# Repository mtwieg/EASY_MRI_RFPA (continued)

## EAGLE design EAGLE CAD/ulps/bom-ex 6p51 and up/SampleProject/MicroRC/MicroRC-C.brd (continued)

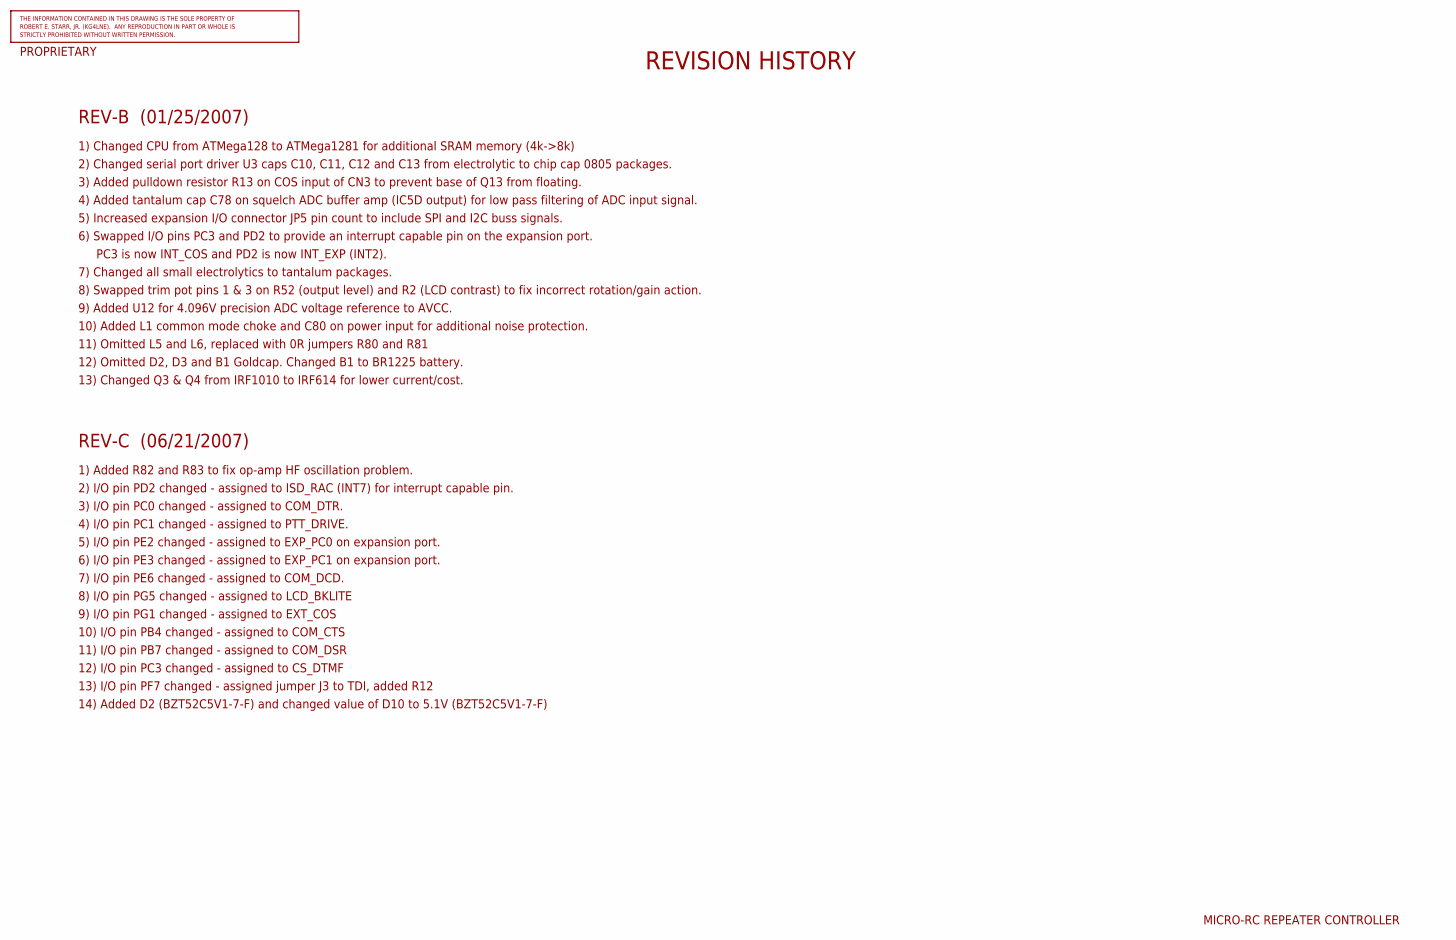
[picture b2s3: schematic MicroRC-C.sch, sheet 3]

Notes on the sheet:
MICRO-RC REPEATER CONTROLLER
REVISION HISTORY
REV-B (01/25/2007)
2) Changed serial port driver U3 caps C10, C11, C12 and C13 from electrolytic to chip cap 0805 packages.
4) Added tantalum cap C78 on squelch ADC buffer amp (IC5D output) for low pass filtering of ADC input signal.
5) Increased expansion I/O connector JP5 pin count to include SPI and I2C buss signals.
3) Added pulldown resistor R13 on COS input of CN3 to prevent base of Q13 from floating.
6) Swapped I/O pins PC3 and PD2 to provide an interrupt capable pin on the expansion port.
PC3 is now INT_COS and PD2 is now INT_EXP (INT2).
7) Changed all small electrolytics to tantalum packages.
8) Swapped trim pot pins 1 & 3 on R52 (output level) and R2 (LCD contrast) to fix incorrect rotation/gain action.
9) Added U12 for 4.096V precision ADC voltage reference to AVCC.
1) Changed CPU from ATMega128 to ATMega1281 for additional SRAM memory (4k->8k)
10) Added L1 common mode choke and C80 on power input for additional noise protection.
11) Omitted L5 and L6, replaced with 0R jumpers R80 and R81
12) Omitted D2, D3 and B1 Goldcap. Changed B1 to BR1225 battery.
13) Changed Q3 & Q4 from IRF1010 to IRF614 for lower current/cost.
REV-C (06/21/2007)
1) Added R82 and R83 to fix op-amp HF oscillation problem.
2) I/O pin PD2 changed - assigned to ISD_RAC (INT7) for interrupt capable pin.
5) I/O pin PE2 changed - assigned to EXP_PC0 on expansion port.
14) Added D2 (BZT52C5V1-7-F) and changed value of D10 to 5.1V (BZT52C5V1-7-F)
4) I/O pin PC1 changed - assigned to PTT_DRIVE.
6) I/O pin PE3 changed - assigned to EXP_PC1 on expansion port.
7) I/O pin PE6 changed - assigned to COM_DCD.
3) I/O pin PC0 changed - assigned to COM_DTR.
8) I/O pin PG5 changed - assigned to LCD_BKLITE
9) I/O pin PG1 changed - assigned to EXT_COS
10) I/O pin PB4 changed - assigned to COM_CTS
11) I/O pin PB7 changed - assigned to COM_DSR
13) I/O pin PF7 changed - assigned jumper J3 to TDI, added R12
12) I/O pin PC3 changed - assigned to CS_DTMF

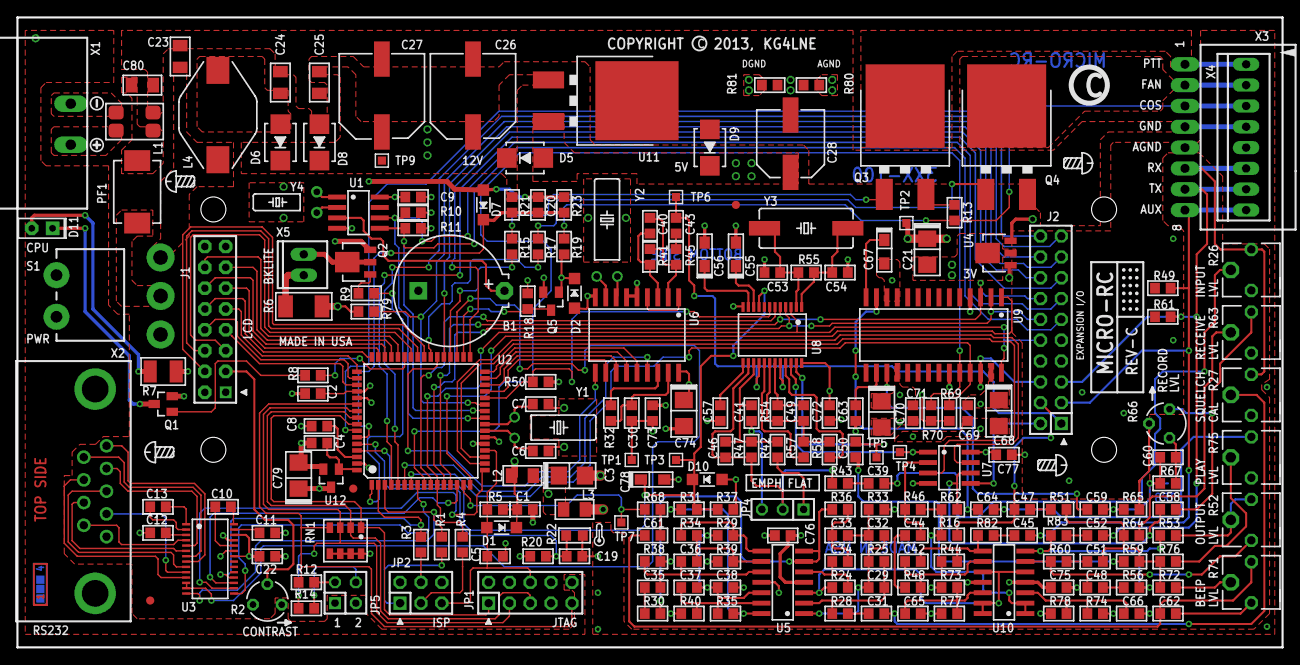
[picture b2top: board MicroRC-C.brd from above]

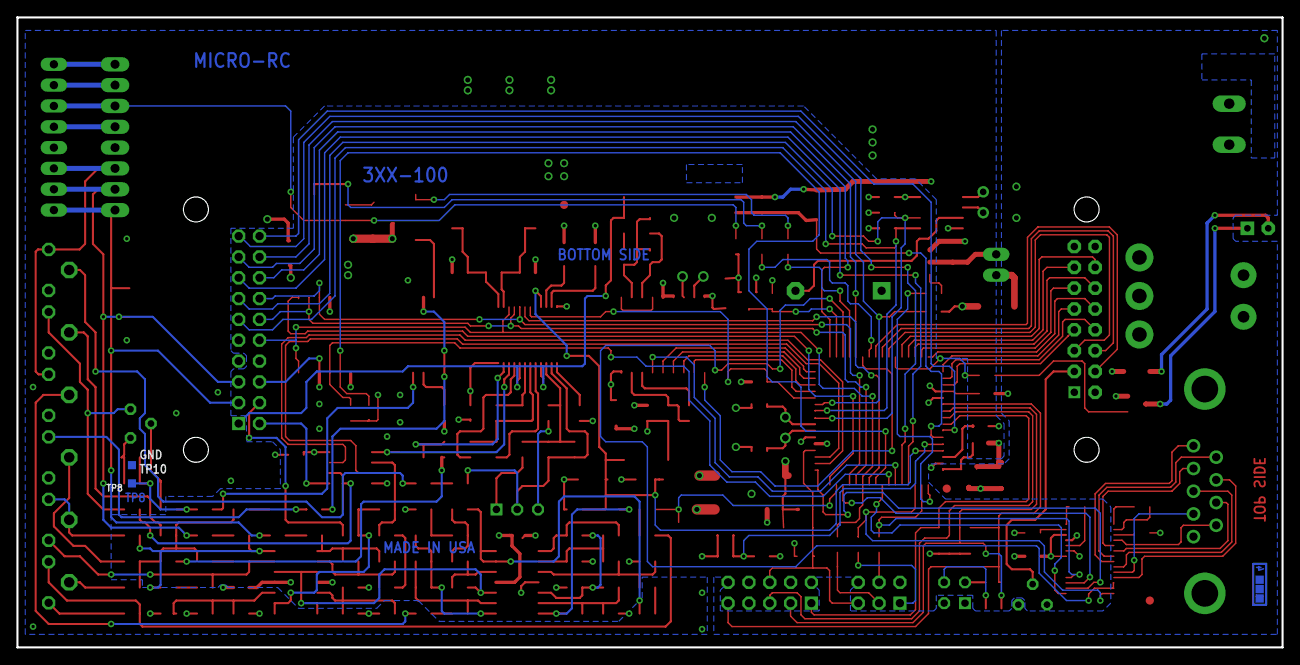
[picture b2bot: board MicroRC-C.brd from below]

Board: 4 copper layers, 154.3 x 76.8 mm, 254 parts (3 on the bottom side), 186 nets.

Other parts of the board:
U$6: ICON_ATTR_COPYRIGHT
U$7: LAYER_CHECK-4
U$60: FIELD_ATTR_DATECODE5_RESTRICT
U$74: ICON_SIDE_BOTTOM
U$75: ICON_SIDE_TOP
U$100: ICON_ATTR_REV-M
U$102: FAB_8X14
U$105: FAB_DOCFIELD
U$112: ICON_TEMP
U$123: ICON_MINUS
U$124: 3.0250; FAB_ARROW_LINE025
U$125: ICON_PLUS
U$128, U$136: 0,0; FAB_ARROW_LINE025
U$132: 2.7125; FAB_CONST_LINE050
U$133, U$239, U$282, U$283: ICON_MSCREW-S
U$138: 6.0750; FAB_ARROW_LINE025
U$139: 0.5750; FAB_CONST_LINE050
U$140: 1.2125; FAB_CONST_LINE050
U$141: 1.5125; FAB_CONST_LINE050
U$142: 1.8125; FAB_CONST_LINE050
U$143: 2.1125; FAB_CONST_LINE050
U$144: 2.4125; FAB_CONST_LINE050
U$145: 1.3375; FAB_CONST_LINE050
U$146: 2.2750; FAB_CONST_LINE050
U$230, U$235, U$280, U$281: ICON_PIN1_B
U$240, U$241: ICON_ARROW-T

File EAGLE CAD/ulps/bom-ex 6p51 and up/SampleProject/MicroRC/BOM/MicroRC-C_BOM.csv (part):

Qty-1,Part References,Value,Package,Mfg Part Num,Mfg Name,VID,Vendor Part Num,Description,Pkg Code,XREF
18,"C2, C8, C9, C10, C19, C20, C30, C31, C43, C57, C63, C69, C71, C72, C73, C75, C76, C77",0.1uF,C0805,C0805F104K5RACTU,Kemet,DK,399-5110-1-ND,CAP CER .1UF 50V X7R 0805 FO,0805,REF69
3,"C23, C24, C25",0.1uF,C1206,C1206C104K5RACTU,Kemet,DK,399-1249-1-ND,CAP .10UF 50V CERAMIC X7R 1206,1206,REF67
0,"C78(DNP)",0.1uF,C3216/T,DNP,DO NOT PLACE,(N/A),DO NOT PLACE,DO NOT PLACE,*,REF14
1,"C55",0.1uF,C3216/T,T491A104K035AT,Kemet,DK,399-3676-1-ND,CAPACITOR TANT .10UF 35V 10% SMD,*,REF22
1,"L2",0.1uH,L1206,PM1210-R10J,JW Miller A Bourns Company,DK,M6093CT-ND,INDUCTOR .10UH 5% 1210 SMD,*,REF20
1,"C80",0.01uF,C1206,12065C103KAT2A,AVX Corporation,DK,478-1542-1-ND,CAP CERM .01UF 10% 50V X7R 1206,*,REF3
1,"C5",0.01uF,C0805,C0805C103K5RACTU,Kemet,DK,399-1158-1-ND,CAP 10000PF 50V CERAMIC X7R 0805,0805,REF66
3,"C11, C12, C13",0.47uF,C0805,C0805F474K3RACTU,Kemet,DK,399-5112-1-ND,CAP CER .47UF 25V X7R 0805 FO,0805,REF74
2,"C40, C62",0.001uF,C0805,C0805C102K5RACTU,Kemet,DK,399-1147-1-ND,CAP 1000PF 50V CERAMIC X7R 0805,0805,REF65
2,"C35, C38",0.047uF,C0805,C0805C473K5RACTU,Kemet,DK,399-1166-1-ND,CAP 47000PF 50V CERAMIC X7R 0805,0805,REF68
1,"C41",0.0068uF,C0805,C0805C682K5RACTU,Kemet,DK,399-1157-1-ND,CAP 6800PF 50V CERAMIC X7R 0805,0805,REF79
2,"R80, R81",0R,R0805,RC0805JR-070RL,Yageo,DK,311-0.0ARCT-ND,RES 0.0 OHM 1/8W 5% 0805 SMD,0805,REF92
2,"R82, R83",1.00K,R0805,ERJ-6ENF1001V,Panasonic - ECG,DK,P1.00KCCT-ND,RES 1.00K OHM 1/8W 1% 0805 SMD,0805,REF45
4,"R16, R46, R55, R62",1M,R0805,ERJ-6ENF1004V,Panasonic - ECG,DK,P1.00MCCT-ND,RES 1.00M OHM 1/8W 1% 0805 SMD,0805,REF46
14,"C1, C22, C39, C44, C45, C47, C50, C52, C58, C59, C61, C64, C65, C66",1uF,C0805,C0805C105Z3VACTU,Kemet,DK,399-1293-1-ND,CAP 1.0UF 25V CERAMIC Y5V 0805,0805,REF73
1,"C67",1uF,C3216/T,T491A105K016AT,Kemet,DK,399-3678-1-ND,CAPACITOR TANT 1.0UF 16V 10% SMD,*,REF23
1,"C56",2.2uF,C3216/T,T491A225K010AT,Kemet,DK,399-3690-1-ND,CAPACITOR TANT 2.2UF 10V 10% SMD,*,REF24
1,"Y2",3.579 MHZ,TC310H,ECS-35-18-10X,ECS Inc,DK,XC1371-ND,CRYSTAL 3.579545 MHZ 18PF CYL,*,REF17
7,"R8, R9, R15, R17, R19, R30, R33",4.75K,R0805,ERJ-6ENF4751V,Panasonic - ECG,DK,P4.75KCCT-ND,RES 4.75K OHM 1/8W 1% 0805 SMD,0805,REF55
1,"Y3",4.032MHZ,SM49,ECS-40.3-20-5PX-TR,ECS Inc,DK,XC1258CT-ND,CRYSTAL 4.032MHZ 20PF SMD,*,REF16
1,"D2",5.1V,SOD123,BZT52C5V1-7-F,Diodes Inc,DK,BZT52C5V1-FDITR-ND,DIODE ZENER 5.1V 500MW SOD-123,SOD123,REF10
1,"R36",5.62K,R0805,ERJ-6ENF5621V,Panasonic - ECG,DK,P5.62KCCT-ND,RES 5.62K OHM 1/8W 1% 0805 SMD,0805,REF59
1,"R38",8.25K,R0805,ERJ-6ENF8251V,Panasonic - ECG,DK,P8.25KCCT-ND,RES 8.25K OHM 1/8W 1% 0805 SMD,0805,REF61
1,"RN1",10K,744-8,744C083103JPTR,CTS Resistor Products,DK,744C083103JPCT-ND,RES ARRAY 10K OHM 8TERM 4RES SMD,*,REF8
19,"R5, R10, R11, R18, R25, R28, R39, R40, R43, R50, R54, R56, R57, R58, R65, R67, R69, R70, R79",10K,R0805,ERJ-6ENF1002V,Panasonic - ECG,DK,P10.0KCCT-ND,RES 10.0K OHM 1/8W 1% 0805 SMD,0805,REF47
5,"R26, R27, R63, R71, R75",10K,EVME-SIDE,EVM-EGGA00B14,Panasonic - ECG,DK,EGG14BK-ND,POT 10K OHM 6MM CERAMIC SIDE ADJ,*,REF42
2,"R2, R66",10K,EVM-L4G,EVM-L4GA00B14,Panasonic - ECG,DK,L4G14BK-ND,POT 10K OHM 4MM CERAMIC TOP ADJ,*,REF44
2,"C4, C51",10uF,C0805,C0805C106K9PACTU,Kemet,DK,399-3138-1-ND,CAP CERAMIC 10UF 6.3V X5R 0805,0805,REF72
3,"C3, C21, C79",10uF,C3528/T,T491B106M016AT,Kemet,DK,399-3708-1-ND,CAPACITOR TANT 10UF 16V 20% SMD,*,REF25
1,"L4",10uH,PM-13,PM3308-100M,JW Miller A Bourns Company,DK,M9719CT-ND,INDUCTOR POWER 10UH SMD,*,REF21
1,"R42",11.3K,R0805,ERJ-6ENF1132V,Panasonic - ECG,DK,P11.3KCCT-ND,RES 11.3K OHM 1/8W 1% 0805 SMD,0805,REF49
1,"Y1",16.000 MHz,TC38H,ECS-160-18-9X,ECS Inc,DK,XC1383-ND,CRYSTAL 16.000 MHZ 18PF CYL,*,REF18
1,"D8",18V,SMB,1SMB5931BT3G,ON Semiconductor,DK,1SMB5931BT3GOSTR-ND,DIODE ZENER 18V 3W SMB,*,REF36
9,"R23, R31, R44, R48, R51, R59, R64, R72, R76",22K,R0805,ERJ-6ENF2212V,Panasonic - ECG,DK,P22.1KCCT-ND,RES 22.1K OHM 1/8W 1% 0805 SMD,0805,REF51
2,"C6, C7",22pF,C0805,C0805C220J5GACTU,Kemet,DK,399-1113-1-ND,CAP CERAMIC 22PF 50V NP0 0805,0805,REF71
3,"C68, C70, C74",22uF,C3528/T,T491B226M016AT,Kemet,DK,399-3717-1-ND,CAPACITOR TANT 22UF 16V 20% SMD,*,REF26
1,"Y4",32.678 kHz,TC26H,ECS-.327-12.5-13X,ECS Inc,DK,X1124-ND,CRYSTAL 32.768 KHZ 12.5PF CYL,*,REF15
2,"R53, R60",33.2K,R0805,ERJ-6ENF3322V,Panasonic - ECG,DK,P33.2KCCT-ND,RES 33.2K OHM 1/8W 1% 0805 SMD,0805,REF53
2,"C53, C54",33pF,C0805,C0805C330J5GACTU,Kemet,DK,399-1115-1-ND,CAP CERAMIC 33PF 50V NP0 0805,0805,REF75
5,"R1, R3, R4, R12, R14",47.5R,R0805,ERJ-6ENF47R5V,Panasonic - ECG,DK,P47.5CCT-ND ,RES 47.5 OHM 1/8W 1% 0805 SMD,0805,REF57
1,"R6",48.7R,R2010,ERJ-12SF48R7U,Panasonic - ECG,DK,P48.7ACCT-ND,RES 48.7 OHM 3/4W 1% 2010 SMD,1210,REF58
1,"R21",62K,R0805,ERJ-6ENF6192V,Panasonic - ECG,DK,P61.9KCCT-ND,RES 61.9K OHM 1/8W 1% 0805 SMD,0805,REF60
1,"R24",91.0K,R0805,ERJ-6ENF9092V,Panasonic - ECG,DK,P90.9KCCT-ND,RES 90.9K OHM 1/8W 1% 0805 SMD,0805,REF62
1,"R47",93.1K,R0805,ERJ-6ENF9312V,Panasonic - ECG,DK,P93.1KCCT-ND,RES 93.1K OHM 1/8W 1% 0805 SMD,0805,REF63
13,"R13, R20, R34, R37, R41, R45, R49, R61, R68, R73, R74, R77, R78",100K,R0805,ERJ-6ENF1003V,Panasonic - ECG,DK,P100KCCT-ND,RES 100K OHM 1/8W 1% 0805 SMD,0805,REF48
3,"C29, C46, C49",100pF,C0805,C0805C101J5GACTU,Kemet,DK,399-1122-1-ND,CAP CERAMIC 100PF 50V NP0 0805,0805,REF64
1,"C28",100uF,CSV-E/F,EEE-1CA101P,Panasonic - ECG,DK,PCE3879CT-ND,CAP ELECT 100UF 16V VS SMD,*,REF80
1,"R35",150K,R0805,ERJ-6ENF1503V,Panasonic - ECG,DK,P150KCCT-ND,RES 150K OHM 1/8W 1% 0805 SMD,0805,REF50
1,"X2",182-009-112-531,NC182M9,182-009-113R531,Norcomp Inc.,DK,182-09ME-ND,CONN DB9 MALE .318"" R/A NICKEL,*,REF34
1,"R52",200K,EVME-SIDE,EVM-EGGA00B25,Panasonic - ECG,DK,EGG25BK-ND,POT 200K OHM 6MM CERAM SIDE ADJ,*,REF43
1,"R32",301K,R0805,ERJ-6ENF3013V,Panasonic - ECG,DK,P301KCCT-ND,RES 301K OHM 1/8W 1% 0805 SMD,0805,REF52
1,"R29",332K,R0805,ERJ-6ENF3323V,Panasonic - ECG,DK,P332KCCT-ND,RES 332K OHM 1/8W 1% 0805 SMD,0805,REF54
1,"R7",464R,R1210,ERJ-14NF4640U,Panasonic - ECG,DK,P464AACT-ND,RES 464 OHM 1/2W 1% 1210 SMD,1210,REF56
2,"C36, C37",470pF,C0805,C0805C471J5GACTU,Kemet,DK,399-1133-1-ND,CAP CERAMIC 470PF 50V NP0 0805,0805,REF76
2,"C26, C27",470uF,CSV-G,EEE-1EA471P,Panasonic - ECG,DK,PCE3909CT-ND,CAP ELECT 470UF 25V VS SMD,*,REF81
1,"C48",560pF,C0805,C0805C561J5GACTU,Kemet,DK,399-1134-1-ND,CAP CERAMIC 560PF 50V NP0 0805,0805,REF78
4,"C32, C33, C34, C42",1500pF,C0805,C0805C152K5RACTU,Kemet,DK,399-1150-1-ND,CAP 1500PF 50V CERAMIC X7R 0805,0805,REF70
1,"C60",4700pF,C0805,C0805C472K5RACTU,Kemet,DK,399-1155-1-ND,CAP 4700PF 50V CERAMIC X7R 0805,0805,REF77
1,"X3",70553-0007,70553-08,70553-0007,Molex Connector Corporation,DK,WM4906-ND,CONN HEADER 8POS .100 R/A GOLD,*,REF30
1,"X5",640454-2,MTA-100-2V,640454-2,Tyco Electronics ,DK,A19423-ND,CONN HEADER VERT 2POS .100 TIN,*,REF87
1,"X4",640454-8,MTA08-100,640454-8,Tyco Electronics ,DK,A19435-ND,CONN HEADER VERT 8POS .100 TIN,*,REF88
1,"U12",AD158X,SOT23,AD1584BRTZ-REEL7,Analog Devices Inc,DK,AD1584BRTZ-REEL7CT-ND,IC V-REF 4.096V SOT-23,SOT23,REF1
1,"D1",BAV16W-7-F,SOD123,BAV16W-7-F,Diodes Inc,DK,BAV16W-FDICT-ND,DIODE SWITCH 75V 400MW SOD123,SOD123,REF9
0,"B1(DNP)",BR1225A/HB,BR1225,BR1225A/HB,Panasonic - BCG,DK,P061-ND,BATTERY LITH COIN HITEMP W/LEGS,*,REF41
2,"D7, D10",BZT52C5V1-7-F,SOD123,BZT52C5V6-7-F,Diodes Inc,DK,BZT52C5V6-FDICT-ND,DIODE ZENER 5.6V 500MW SOD-123,SOD123,REF11
1,"S1",CK-A,CK-A,2M1-SP1-T2-B4-M6RE,Carling Technologies,DK,432-1164-ND,SW TOGGLE SPDT .4VA RT ANG PCB,*,REF5
1,"L1",CM1812,CM1812,CM1812R600R-10,Laird-Signal Integrity Products,DK,240-2454-1-ND,CHOKE COMMON MODE 60 OHMS SMD,*,REF27
1,"U6",CM8870CS,SO18W,MT8870DS,Zarlink,FE,MT8870DS,DTMF Decoder IC,*,REF93
1,"U1",DS1307Z,SO08,DS1307Z+,Maxim Integrated Products,DK,DS1307Z+-ND,IC RTC SERIAL 512K 8-SOIC,SO08,REF28
1,"X1",EDSTLZ951/2,951-2,EDSTLZ951/2,On Shore Technology Inc,DK,ED2427-ND,TERM BLOCK HDR 5.08MM 2POS PCB,*,REF39
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
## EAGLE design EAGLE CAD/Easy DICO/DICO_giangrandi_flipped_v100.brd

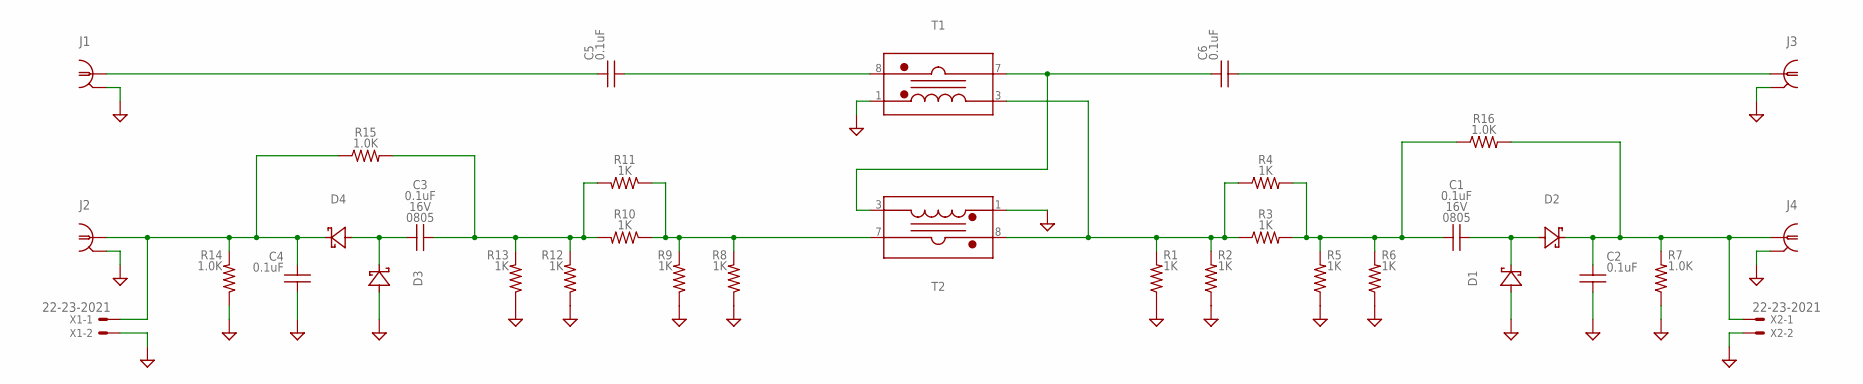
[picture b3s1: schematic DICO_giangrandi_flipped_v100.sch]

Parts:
C1, C2, C3, C4: 0.1uF; 0805_IPC-7351B
C5, C6: 0.1uF; C1812
D1, D2, D3, D4: D-SCHOTTKY1N5711W-7-FSOD123; SOD123
J1, J2, J3, J4: COAXSMA_0.375WIDE; SMA_EDGE_0.375WIDE
R1, R2, R3, R4, R5, R6, R8, R9, R10, R11, R12, R13: 1K; 1206_IPC-7351B
R7, R14, R15, R16: 1.0K; 0805_IPC-7351B
T1, T2: TRAFO_CURRENTSENSEPA1005_NOCENTERPADS; PA1005_NOCENTERPADS
X1, X2: 22-23-2021

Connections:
GND: C2.2, C4.2, D1.A (A1), D3.A (A1), J1.S1 (GND1), J1.S2 (GND1), J1.S3 (GND1), J1.S4 (GND1), J2.S1 (GND1), J2.S2 (GND1), J2.S3 (GND1), J2.S4 (GND1), J3.S1 (GND1), J3.S2 (GND1), J3.S3 (GND1), J3.S4 (GND1), J4.S1 (GND1), J4.S2 (GND1), J4.S3 (GND1), J4.S4 (GND1), R1.2, R2.2, R5.2, R6.2, R7.2, R8.2, R9.2, R12.2, R13.2, R14.2, T1.1 (SS), T2.1 (SS), X1.2, X2.2
unnamed: R8.1, R9.1, R10.1, R11.1, T2.7 (PF)
unnamed: C5.2, T1.8 (PS)
unnamed: C5.1, J1.C (1)
unnamed: C1.1, R3.2, R4.2, R5.1, R6.1, R16.1
unnamed: C1.2, D1.K (C1), D2.A (A1)
unnamed: C2.1, D2.K (C1), J4.C (1), R7.1, R16.2, X2.1
unnamed: C3.1, R10.2, R11.2, R12.1, R13.1, R15.2
unnamed: C3.2, D3.K (C1), D4.A (A1)
unnamed: C4.1, D4.K (C1), J2.C (1), R14.1, R15.1, X1.1
unnamed: C6.2, J3.C (1)
unnamed: R1.1, R2.1, R3.1, R4.1, T1.3 (SF), T2.8 (PS)
unnamed: C6.1, T1.7 (PF), T2.3 (SF)

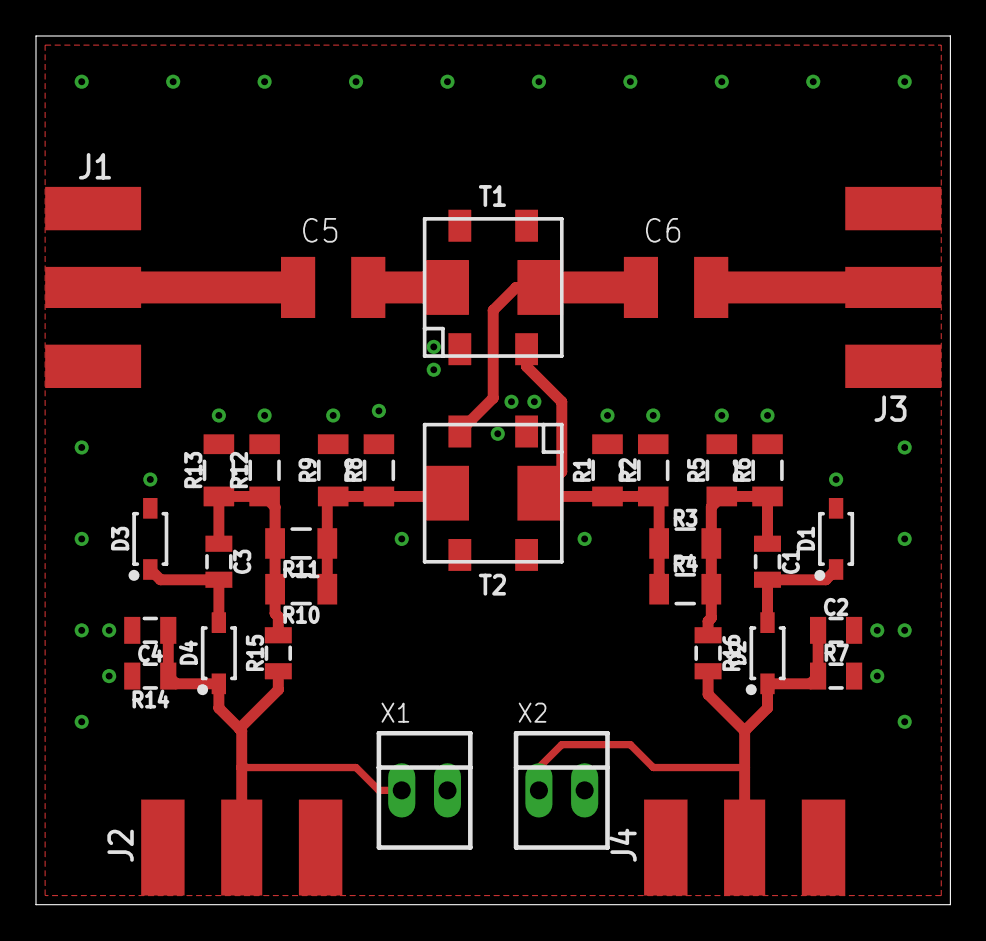
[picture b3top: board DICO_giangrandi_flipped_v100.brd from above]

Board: 2 copper layers, 50.8 x 48.3 mm, 34 parts (0 on the bottom side), 13 nets.

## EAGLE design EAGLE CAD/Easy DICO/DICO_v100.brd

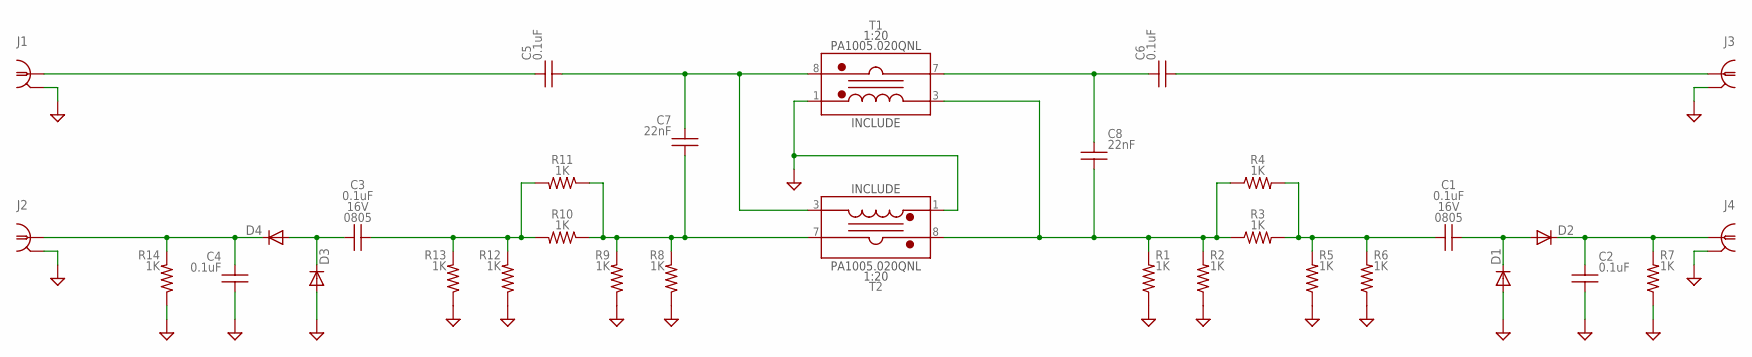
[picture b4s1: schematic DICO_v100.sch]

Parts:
C1, C2, C3, C4: 0.1uF; 0805_IPC-7351B
C5, C6: 0.1uF; C1812
C7, C8: 22nF; C1206
D1, D2, D3, D4: DIODE-SOD123; SOD123
J1, J2, J3, J4: COAXBNC_EDGE; BNC_EDGE
R1, R2, R3, R4, R5, R6, R7, R8, R9, R10, R11, R12, R13, R14: 1K; R1206
T1, T2: TRAFO_CURRENTSENSEPA1005.020QNLPA1005; PA1005

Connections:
GND: C2.2, C4.2, D1.A, D3.A, J1.G1 (GND1), J1.G2 (GND1), J1.G3 (GND1), J1.G4 (GND1), J2.G1 (GND1), J2.G2 (GND1), J2.G3 (GND1), J2.G4 (GND1), J3.G1 (GND1), J3.G2 (GND1), J3.G3 (GND1), J3.G4 (GND1), J4.G1 (GND1), J4.G2 (GND1), J4.G3 (GND1), J4.G4 (GND1), R1.2, R2.2, R5.2, R6.2, R7.2, R8.2, R9.2, R12.2, R13.2, R14.2, T1.1 (SS), T2.1 (SS)
unnamed: C8.2, R1.1, R2.1, R3.1, R4.1, T1.3 (SF), T2.8 (PS)
unnamed: C5.2, C7.1, T1.8 (PS), T2.3 (SF)
unnamed: C6.1, C8.1, T1.7 (PF)
unnamed: C5.1, J1.C (1)
unnamed: C1.1, R3.2, R4.2, R5.1, R6.1
unnamed: C1.2, D1.C, D2.A
unnamed: C2.1, D2.C, J4.C (1), R7.1
unnamed: C7.2, R8.1, R9.1, R10.1, R11.1, T2.7 (PF)
unnamed: C3.1, R10.2, R11.2, R12.1, R13.1
unnamed: C3.2, D3.C, D4.A
unnamed: C4.1, D4.C, J2.C (1), R14.1
unnamed: C6.2, J3.C (1)

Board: 2 copper layers, 32 parts (0 on the bottom side), 13 nets, no tracks yet.

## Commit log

2022-04-02 Ignore backup files
2022-04-02 Fix gitignores
2022-04-02 eagle .brd and .sch files
2022-04-02 LTSPICE gitignore
2022-04-02 ltspice folder
2022-04-02 component datasheets
2022-04-02 CAM folder contents
2022-04-02 eagle libraries
2022-04-02 eagle .cam files
2022-04-02 folders for measurements and photos
2022-04-02 Work on IRF630 PA
    Also add FET_parameters_sheet.csv
    add IRF520 and IRF520N datasheets
2022-04-02 Change Ldamp from 150nH to 47nH
2022-04-02 Update component values for gate bias driver
    Change C209 from 220pF to 330pF
2022-04-02 Done testing for today
    Seem to be getting significant loss across baluns
    Measured input balun leakage at ~650nH (primary referred, both secondaries shorted to gnd)
2022-04-04 Assembly variants
    Try adding a couple to the schematic...
2022-04-04 tidy up sims a bit
    Put all models and subcircuits in a separate folder
    Create one file which includes all of them
    Reference that file in each sim
    Also use the "fetprops" files in all the existing simulations
2022-04-04 more assembly variant work....
2022-04-04 bias controller update
2022-04-04 Updated IRF520N and IRF630 designs
2022-04-05 raw scope data dump
2022-04-05 change a couple bias driver components
    need to rework the 01 board like this too
2022-04-05 More schematic editing
    Add DR127 to my library
    More assembly variant component values
2022-04-06 Work on libraries...
2022-04-06 run renumber_sheet, make this v106
2022-04-06 Add my extra info layers to all my libraries
2022-04-06 copy "R" variants to "R90"
2022-04-06 ltspice screenshots for presentation
    also create plot settings for tran sims
2022-04-06 More schematic/library changes
2022-04-06 Thermal camera measurements
2022-04-07 add photos
2022-04-08 characterization data and plots
2022-04-08 try transformer model in spice
2022-04-09 stuff for presentation
2022-04-09 more refinement of hp4 model
2022-04-09 working on dico again
2022-04-09 save eagle and commit again...
2022-04-09 simulate different ways to connect tandem match dico
2022-04-09 DICO layout
2022-04-09 put DICO eagle files in separate folder
2022-04-09 ignore .net and .log files (from LTspice)
    Also delete the existing files
2022-04-10 dico and detector work
2022-04-12 Resort eagle folder
    Divide RFPA into revA and revB folders
    Delete other versions
2022-04-12 adding more technologies...
2022-04-12 more technologies....
2022-04-13 jellybean component values
2022-04-13 stop values from reverting on jellybean Rs
2022-04-13 Do same for capacitor library
2022-04-14 More part attributes....
2022-04-14 EXCLUDEs and INCLUDEs
2022-04-14 bom-ex export working
    Need to use tab-delimited format due to parts with commas in partno....
2022-04-14 Tidying up revA schematic
2022-04-14 Finishing off revA S2...
    Rename files and folder
    Fix DRCs errors caused by changing footprints
2022-04-14 export schematic and BOM for revA S2
2022-04-14 Copy S1 to S2
2022-04-14 S1 component values
    Change component values for S1
    Also fix a couple in S2
    Export BOM and pdf for S1
2022-04-16 Copy revA S2 to new revB S2
2022-04-16 Work on revB
    revB is basically the same as revA, except will have soldermask and silkscreen. Some components are moved around to make room for labels. Name labels updated in libraries.
2022-04-16 Add thermal pads and heatsink clips to schematic
    Also modify bom-ex old.ulp to not ignore parts which lack a package but have a part number
2022-04-16 Copy the pads and clips to revA S1 and S2
2022-04-17 Better docfield
    I modified my docfield symbol (not included in the repo!)
    I define a few global attributes:
    BOMREV
    FABREV
    AUTHOR
    DRAWING_NUMBER
2022-04-17 Will have to place sheet names manually...
2022-04-17 revised parametric spice sim
    here I define the single ended source/load impedances, and the balun turns ratios, initially, rather than having them be derived from other parameters
2022-04-17 add my transformer model
2022-04-17 fix bandpass errors in tran simulation
    increasing characteristic impedance of bpf helped a lot, for some reason.
    also setting reltol to 0.0001 help
    also used pi instead of 3.14159...
2022-04-17 ltspice demo
    writing up the wiki section on ltspice
    also some screenshots
2022-04-17 more screenshots for wiki
2022-04-18 re-export boms
    one of the FETs in S1 had irf520n as the value?
2022-04-18 Add global attributes and sheet names
2022-04-18 Add modified frames library
2022-04-18 Replace frames and re-print pdfs
2022-04-30 Export revB CAM files and readme
    Also update a few images for the slides
2022-05-16 Disclaimer
2022-06-04 Work on revC
2022-06-12 Move connectors/LEDs/buttons to west edge
    Aiming to have these poke through a panel.
2022-06-14 Try and keep area under 30 square inches
2022-06-17 resolve issue with L1
    eagle was complaining about assembly variant not defined in schematic...?
2022-06-17 Slip around S2 layout
    Fits better with surroundings
2022-06-18 cleaning up revC
    fixed all major DRC errors
    returned all nets to default class
    all airwires routed
2022-06-18 Output balun section
    To save space, remove C119 and C120, replace with 1206 resistors instead to select turns ratio
    Put all drain bias inductors back on top side
    Add keepouts to inductor packages
    Move R44-47 to centerline, away from FETs
2022-06-18 Add bypass cap for VB near S2 bias Add 40mm wide heatsink to library adjust some trace widths
2022-06-18 24V regulator
    Add discrete 24V linear regulator in schematic
    Using one of my TO220 FETs for the pass device for now
    Added TL431 to VREF library
    Also added two more mounting holes to board
    And the footprint for a clip-on TO-220 heatsink
2022-06-18 Put discrete LDO on board
    Remove old zeners
    Move smaller electrolytic caps towards load circuitry to free up space
    Move extra mounting holes onto board
    Should consider reordering buttons/LEDs on west edge
2022-06-19 TIP122 and angle bracket
2023-07-25 add license
